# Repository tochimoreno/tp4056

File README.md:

# Batery charger with TP4056, protection and power path
forked from ...

Tomo el proyecto original como base para realizar uno nuevo que incluya un power path para mejor funcionamiento del cargador.

* Clean up and redraw the schematic
* Add power path
* Remove KiCad v5 files
* Add 3V3 LDO regulator
* Add divisor for measurment Bat voltage

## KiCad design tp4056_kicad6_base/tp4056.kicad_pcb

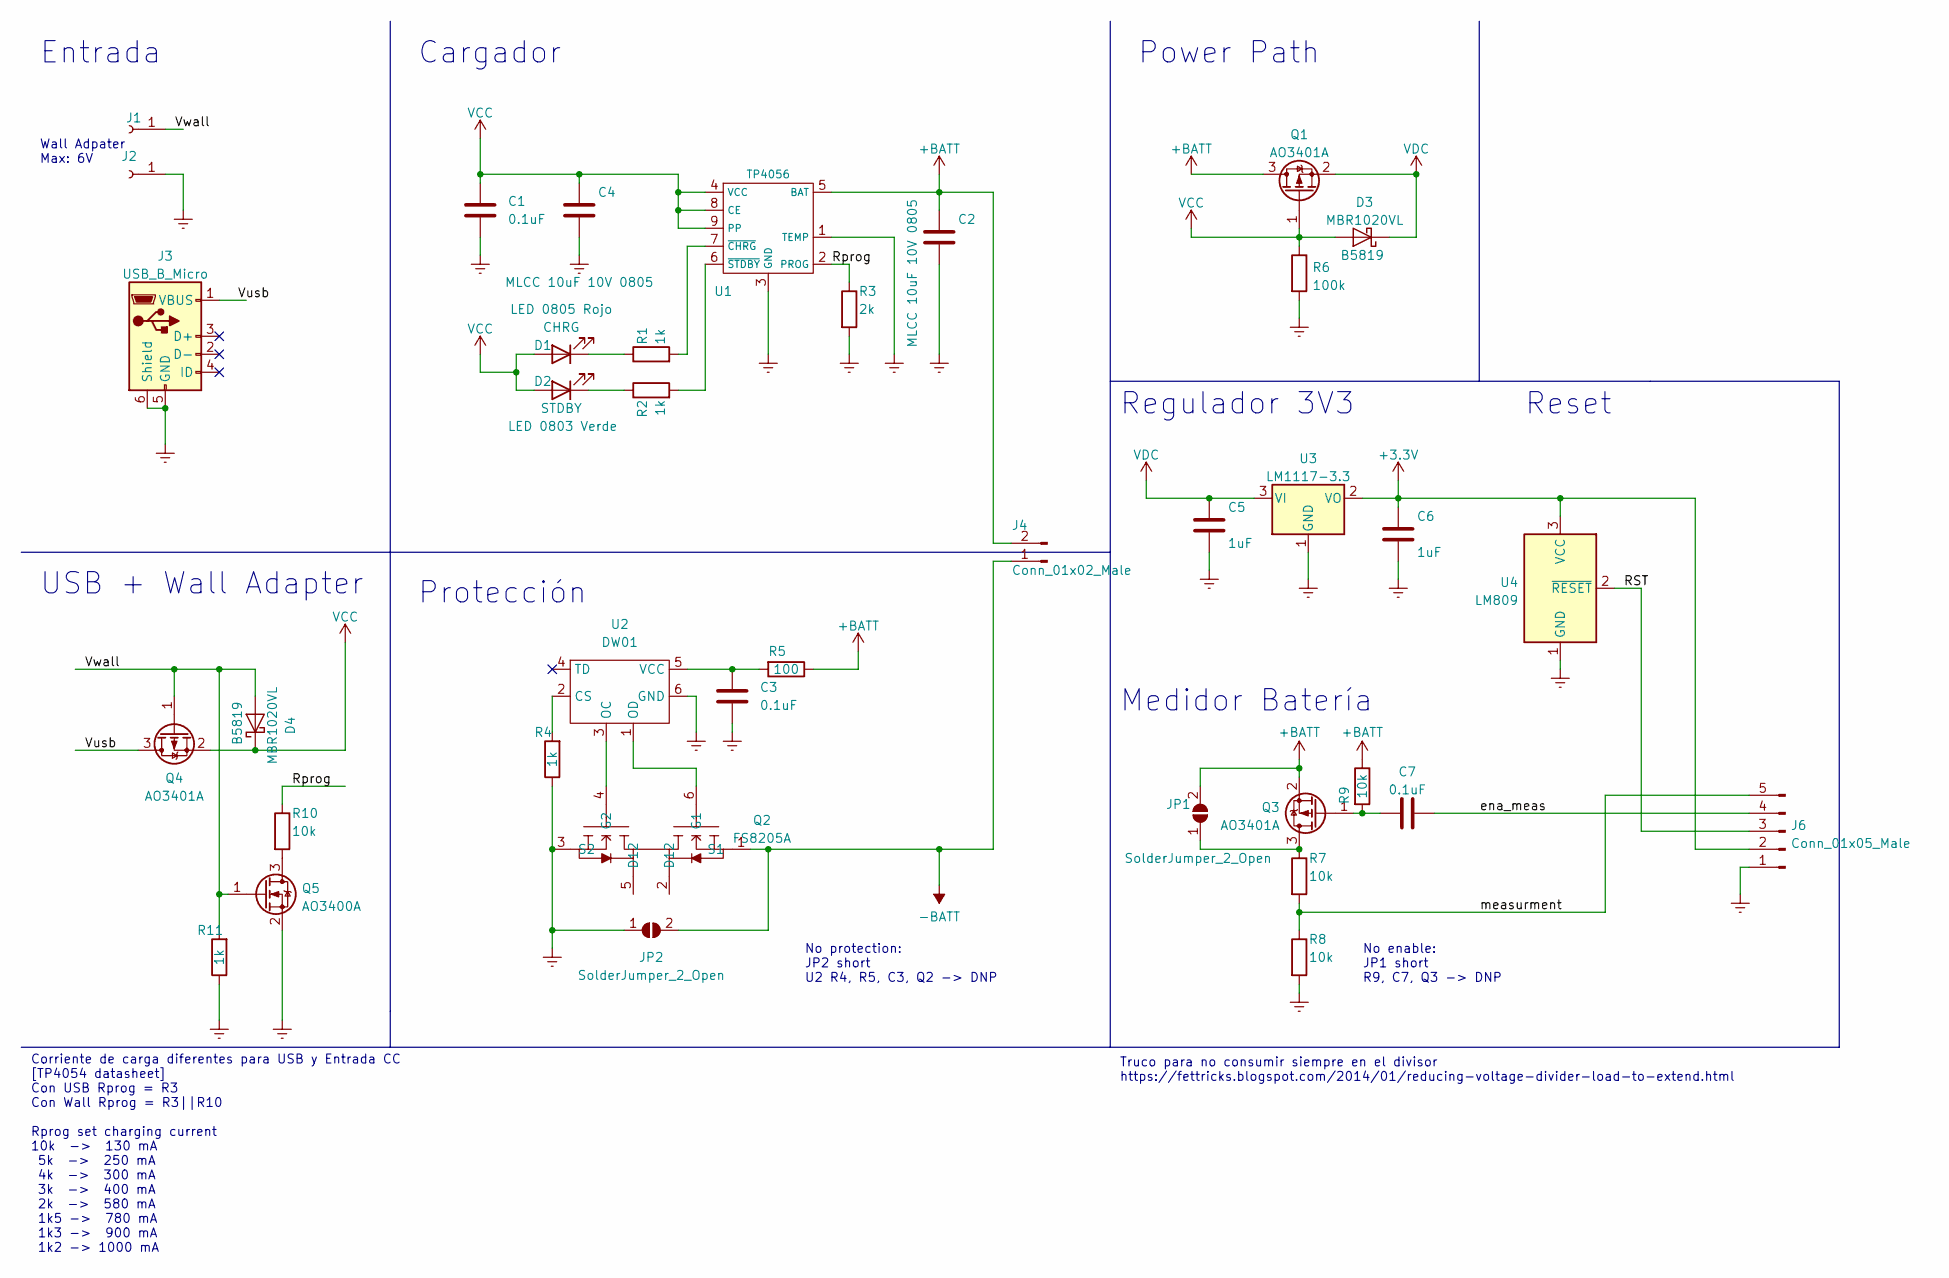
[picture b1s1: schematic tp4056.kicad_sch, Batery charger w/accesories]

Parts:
C1, C3, C7: 0.1uF; C_0805_2012Metric
C2, C4: MLCC 10uF 10V 0805; C_0805_2012Metric
C5, C6: 1uF; C_0805_2012Metric
D1: LED 0805 Rojo; LED_0805_2012Metric_Pad1.15x1.40mm_HandSolder
D2: LED 0803 Verde; LED_0805_2012Metric_Pad1.15x1.40mm_HandSolder
D3, D4: MBR1020VL; D_SOD-123F
J1, J2: Conn_01x01_Female; PinSocket_1x01_P2.54mm_Vertical
J3: USB_B_Micro; USB_Micro-B_Molex-105017-0001
J4: Conn_01x02_Male; JST_EH_B2B-EH-A_1x02_P2.50mm_Vertical
J6: Conn_01x05_Male; JST_EH_B5B-EH-A_1x05_P2.50mm_Vertical
JP1, JP2: SolderJumper_2_Open; SolderJumper-2_P1.3mm_Open_TrianglePad1.0x1.5mm
Q1, Q3, Q4: AO3401A; SOT-23
Q2: FS8205A; SOT-23-6
Q5: AO3400A; SOT-23
R1, R2, R4, R11: 1k; R_0805_2012Metric
R3: 2k; R_0805_2012Metric
R5: 100; R_0805_2012Metric
R6: 100k; R_0805_2012Metric
R7, R8, R9, R10: 10k; R_0805_2012Metric
U1: TP4056; SOIC-8-1EP_3.9x4.9mm_P1.27mm_EP2.29x3mm
U2: DW01; SOT-23-6
U3: LM1117-3.3; SOT-23
U4: LM809; SOT-23

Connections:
+3.3V: C6.1, J6.2, U3.2 (VO), U4.3 (VCC)
+BATT: C2.1, J4.2, JP1.2 (B), Q1.3 (D), Q3.2 (S), R5.1, R9.1, U1.5 (BAT)
-BATT: J4.1, JP2.2 (B), Q2.1 (S1)
/RST: J6.3, U4.2 (~RESET)
/Rprog: R3.1, R10.1, U1.2 (PROG)
/Vusb: J3.1 (VBUS), Q4.3 (D)
/Vwall: D4.2 (A), J1.1, Q4.1 (G), Q5.1 (G), R11.2
/ena_meas: C7.2, J6.4
/measurment: J6.5, R7.2, R8.1
Earth: C1.2, C2.2, C3.2, C4.2, C5.2, C6.2, J2.1, J3.5 (GND), J3.6 (Shield), J6.1, JP2.1 (A), Q2.3 (S2), Q5.2 (S), R3.2, R4.1, R6.2, R8.2, R11.1, U1.1 (TEMP), U1.3 (GND), U2.6 (GND), U3.1 (GND), U4.1 (GND)
unnamed: C3.1, R5.2, U2.5 (VCC)
unnamed: C7.1, Q3.1 (G), R9.2
unnamed: D1.1 (K), R1.1
unnamed: D2.1 (K), R2.1
unnamed: JP1.1 (A), Q3.3 (D), R7.1
unnamed: Q2.4 (G2), U2.3 (OC)
unnamed: Q2.6 (G1), U2.1 (OD)
unnamed: Q5.3 (D), R10.2
unnamed: R1.2, U1.7 (~CHRG)
unnamed: R2.2, U1.6 (~STDBY)
unnamed: R4.2, U2.2 (CS)
VDC: C5.1, D3.1 (K), Q1.2 (S), U3.3 (VI)

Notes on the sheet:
Power Path
Corriente de carga diferentes para USB y Entrada CC [TP4054 datasheet] Con USB Rprog = R3 Con Wall Rprog = R3||R10 Rprog set charging current 10k -> 130 mA 5k -> 250 mA 4k -> 300 mA 3k -> 400 mA 2k -> 580 mA 1k5 -> 780 mA 1k3 -> 900 mA 1k2 -> 1000 mA
No protection: JP2 short U2 R4, R5, C3, Q2 -> DNP
Medidor Batería
USB + Wall Adapter
Reset
Truco para no consumir siempre en el divisor https://fettricks.blogspot.com/2014/01/reducing-voltage-divider-load-to-extend.html
Cargador
Protección
Entrada
Wall Adpater Max: 6V
No enable: JP1 short R9, C7, Q3 -> DNP
Regulador 3V3

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
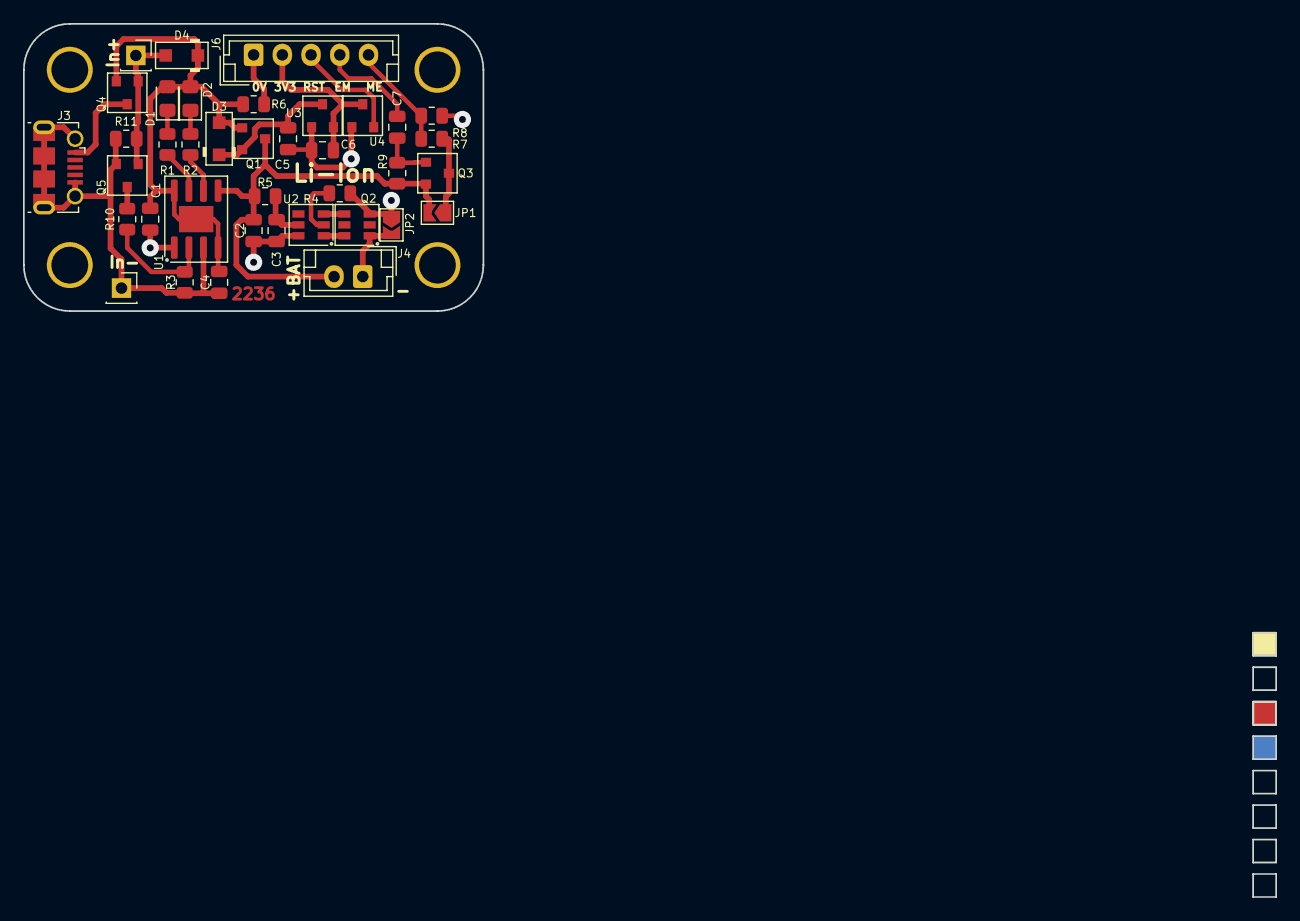
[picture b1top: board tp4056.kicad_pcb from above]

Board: 2 copper layers, 109.0 x 76.0 mm, 38 parts (0 on the bottom side), 23 nets.

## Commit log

2022-08-01 redraw and add power path
2022-08-01 fix output path
2022-08-02 remove KiCad v5 files
2022-08-02 remove output images
2022-08-02 add Rprog table
2022-08-19 add 3v3 regulator
2022-08-20 Add 3.3V LDO regulator
2022-08-20 Cambios estéticos en el sch
2022-08-20 mod README.md
2022-08-20 pcd.Add board and position elements
2022-08-20 git ignore update
2022-08-20 pcb. Board ready in 4032
2022-08-20 pcb. Board 38x18
2022-08-21 sch. add voltage supervisor.
2022-08-21 pcb. board 40x20 one layer
2022-08-21 finish version 44x19mm
2022-08-22 pcb. new version 29x23. OJO Revisar disponibilidad de MOSFET!
2022-08-23 sch. redraw and organization
2022-08-30 Add zero-power measurment. Some connectors change.
2022-09-04 Change conectors. Add jumpers. PCB ready 48x20.
2022-09-04 PCB update
2022-09-05 PCB 40x32
2022-09-07 PCB 40x25. To check DRC
2022-09-13 SCH. Add USB and Wall Power Adaptor
2022-09-14 PCB. 40x25. Add wall adpapter option. To final check.
2022-09-14 PCB. output files. minor cosmetic changes.
